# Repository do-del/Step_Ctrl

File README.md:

# Step_Ctrl
向XDrive和稚晖君的STEP-CTRL学习项目

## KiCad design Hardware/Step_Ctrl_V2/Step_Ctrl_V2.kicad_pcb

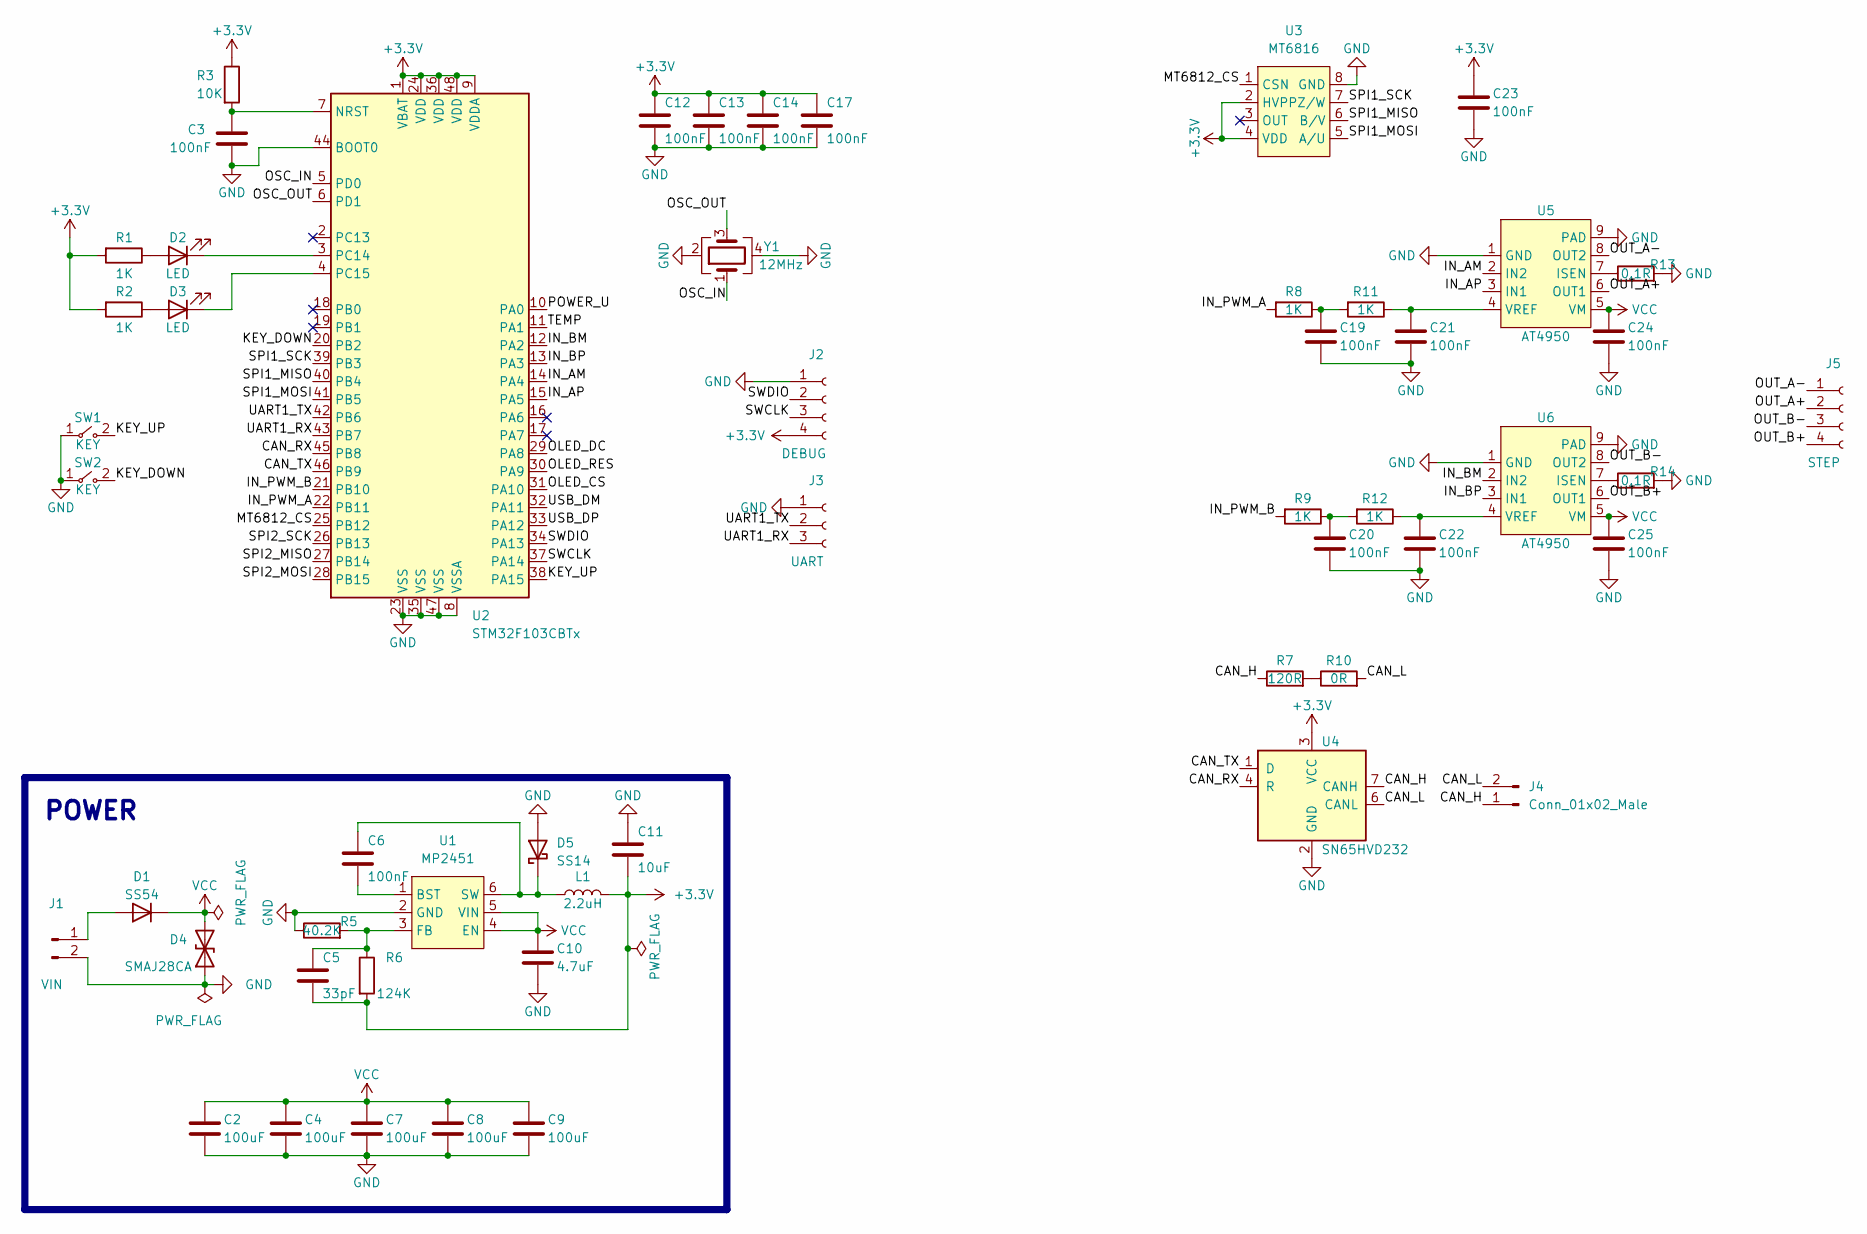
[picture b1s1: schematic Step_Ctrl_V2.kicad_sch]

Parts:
C2, C4, C7, C8, C9: 100uF; C_1210_3225Metric
C3, C6, C12, C13, C14, C17, C19, C20, C21, C22, C23, C24, C25: 100nF; C_0603_1608Metric_Pad1.08x0.95mm_HandSolder
C5: 33pF; C_0603_1608Metric_Pad1.08x0.95mm_HandSolder
C10: 4.7uF; C_0603_1608Metric_Pad1.08x0.95mm_HandSolder
C11: 10uF; C_0603_1608Metric_Pad1.08x0.95mm_HandSolder
D1: SS54; D_SMA
D2, D3: LED; LED_0603_1608Metric_Pad1.05x0.95mm_HandSolder
D4: SMAJ28CA; D_SMA
D5: SS14; D_SOD-323
J1: VIN; PH2.0mm-2P-WT
J2: DEBUG; JST_SH_SM04B-SRSS-TB_1x04-1MP_P1.00mm_Horizontal
J3: UART; JST_SH_SM03B-SRSS-TB_1x03-1MP_P1.00mm_Horizontal
J4: Conn_01x02_Male; SH1.0_01x02P_WT
J5: STEP; PH2.0mm-4P-WT
L1: 2.2uH; IND_CD32
R1, R2, R8, R9, R11, R12: 1K; R_0603_1608Metric_Pad0.98x0.95mm_HandSolder
R3: 10K; R_0603_1608Metric_Pad0.98x0.95mm_HandSolder
R5: 40.2K; R_0603_1608Metric_Pad0.98x0.95mm_HandSolder
R6: 124K; R_0603_1608Metric_Pad0.98x0.95mm_HandSolder
R7: 120R; R_0603_1608Metric_Pad0.98x0.95mm_HandSolder
R10: 0R; R_0402_1005Metric
R13, R14: 0.1R; R_1206_3216Metric
SW1, SW2: KEY; SW_3x4
U1: MP2451; SOT-23-6
U2: STM32F103CBTx; LQFP-48_7x7mm_P0.5mm
U3: MT6816; SOP-8
U4: SN65HVD232; SOIC-8_3.9x4.9mm_P1.27mm
U5, U6: AT4950; ESOP8L
Y1: 12MHz; Crystal_SMD_3225-4Pin_3.2x2.5mm

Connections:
+3V3: C5.2, C11.1, C12.1, C13.1, C14.1, C17.1, C23.1, J2.4, L1.2, R1.2, R2.2, R3.1, R6.2, U2.1 (VBAT), U2.9 (VDDA), U2.24 (VDD), U2.36 (VDD), U2.48 (VDD), U3.2 (HVPP), U3.4 (VDD), U4.3 (VCC)
/CAN_H: J4.1, R7.1, U4.7 (CANH)
/CAN_L: J4.2, R10.2, U4.6 (CANL)
/CAN_RX: U2.45 (PB8), U4.4 (R)
/CAN_TX: U2.46 (PB9), U4.1 (D)
/IN_AM: U2.14 (PA4), U5.2 (IN2)
/IN_AP: U2.15 (PA5), U5.3 (IN1)
/IN_BM: U2.12 (PA2), U6.2 (IN2)
/IN_BP: U2.13 (PA3), U6.3 (IN1)
/IN_PWM_A: R8.2, U2.22 (PB11)
/IN_PWM_B: R9.2, U2.21 (PB10)
/KEY_DOWN: SW2.2 (B), U2.20 (PB2)
/KEY_UP: SW1.2 (B), U2.38 (PA15)
/MT6812_CS: U2.25 (PB12), U3.1 (CSN)
/OLED_CS: U2.31 (PA10)
/OLED_DC: U2.29 (PA8)
/OLED_RES: U2.30 (PA9)
/OSC_IN: U2.5 (PD0), Y1.1
/OSC_OUT: U2.6 (PD1), Y1.3
/OUT_A+: J5.2, U5.6 (OUT1)
/OUT_A-: J5.1, U5.8 (OUT2)
/OUT_B+: J5.4, U6.6 (OUT1)
/OUT_B-: J5.3, U6.8 (OUT2)
/POWER_U: U2.10 (PA0)
/SPI1_MISO: U2.40 (PB4), U3.6 (B/V)
/SPI1_MOSI: U2.41 (PB5), U3.5 (A/U)
/SPI1_SCK: U2.39 (PB3), U3.7 (Z/W)
/SPI2_MISO: U2.27 (PB14)
/SPI2_MOSI: U2.28 (PB15)
/SPI2_SCK: U2.26 (PB13)
/SWCLK: J2.3, U2.37 (PA14)
/SWDIO: J2.2, U2.34 (PA13)
/TEMP: U2.11 (PA1)
/UART1_RX: J3.3, U2.43 (PB7)
/UART1_TX: J3.2, U2.42 (PB6)
/USB_DM: U2.32 (PA11)
/USB_DP: U2.33 (PA12)
GND: C2.2, C3.2, C4.2, C7.2, C8.2, C9.2, C10.2, C11.2, C12.2, C13.2, C14.2, C17.2, C19.2, C20.2, C21.2, C22.2, C23.2, C24.2, C25.2, D4.1 (A1), D5.2 (A), J1.2, J2.1, J3.1, R5.1, R13.2, R14.2, SW1.1 (A), SW2.1 (A), U1.2 (GND), U2.8 (VSSA), U2.23 (VSS), U2.35 (VSS), U2.44 (BOOT0), U2.47 (VSS), U3.8 (GND), U4.2 (GND), U5.1 (GND), U5.9 (PAD), U6.1 (GND), U6.9 (PAD), Y1.2, Y1.4
unnamed: C3.1, R3.2, U2.7 (NRST)
unnamed: C5.1, R5.2, R6.1, U1.3 (FB)
unnamed: C6.1, D5.1 (K), L1.1, U1.6 (SW)
unnamed: C6.2, U1.1 (BST)
unnamed: C19.1, R8.1, R11.2
unnamed: C20.1, R9.1, R12.2
unnamed: C21.1, R11.1, U5.4 (VREF)
unnamed: C22.1, R12.1, U6.4 (VREF)
unnamed: D1.2 (A), J1.1
unnamed: D2.1 (K), U2.3 (PC14)
unnamed: D2.2 (A), R1.1
unnamed: D3.1 (K), U2.4 (PC15)
unnamed: D3.2 (A), R2.1
unnamed: R7.2, R10.1
unnamed: R13.1, U5.7 (ISEN)
unnamed: R14.1, U6.7 (ISEN)
VCC: C2.1, C4.1, C7.1, C8.1, C9.1, C10.1, C24.1, C25.1, D1.1 (K), D4.2 (A2), U1.4 (EN), U1.5 (VIN), U5.5 (VM), U6.5 (VM)

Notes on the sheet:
POWER

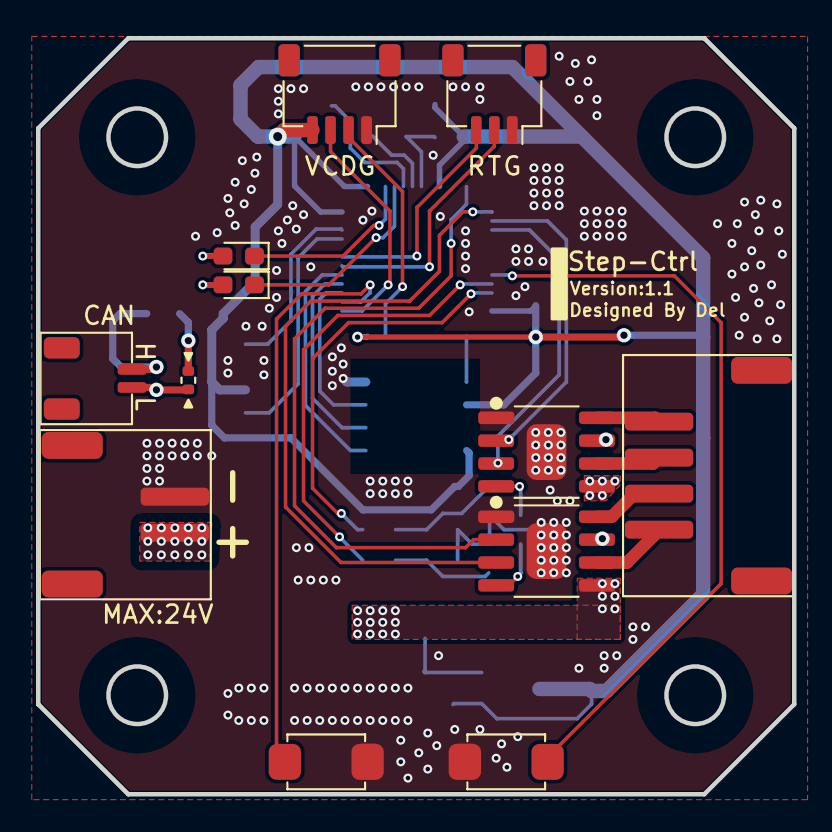
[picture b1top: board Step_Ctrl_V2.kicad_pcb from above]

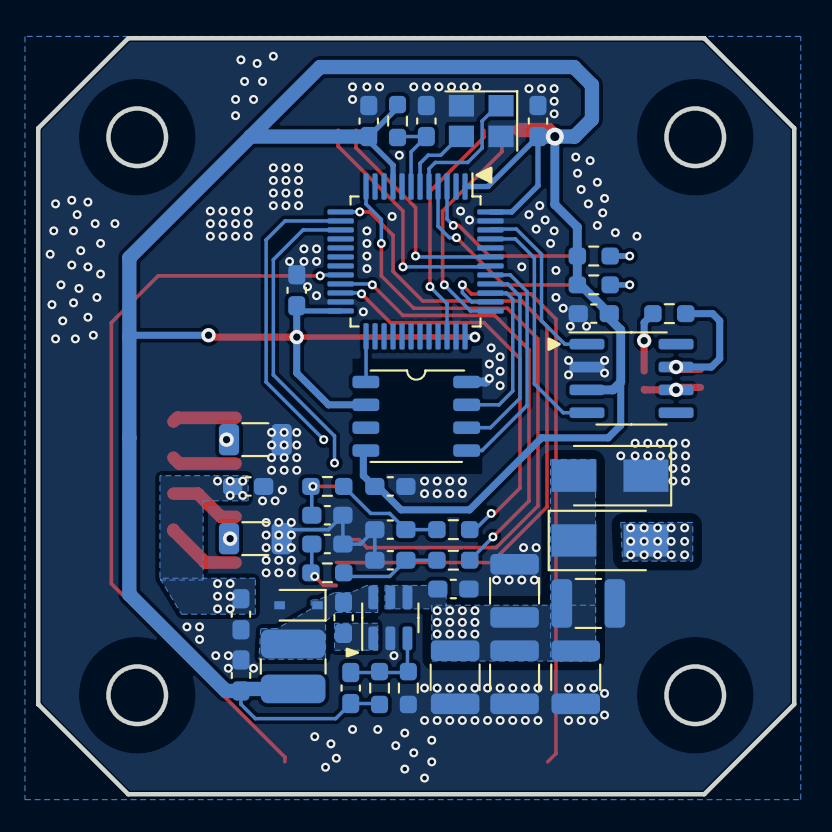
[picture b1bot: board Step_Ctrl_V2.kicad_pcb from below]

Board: 2 copper layers, 42.0 x 42.0 mm, 54 parts (42 on the bottom side), 45 nets.

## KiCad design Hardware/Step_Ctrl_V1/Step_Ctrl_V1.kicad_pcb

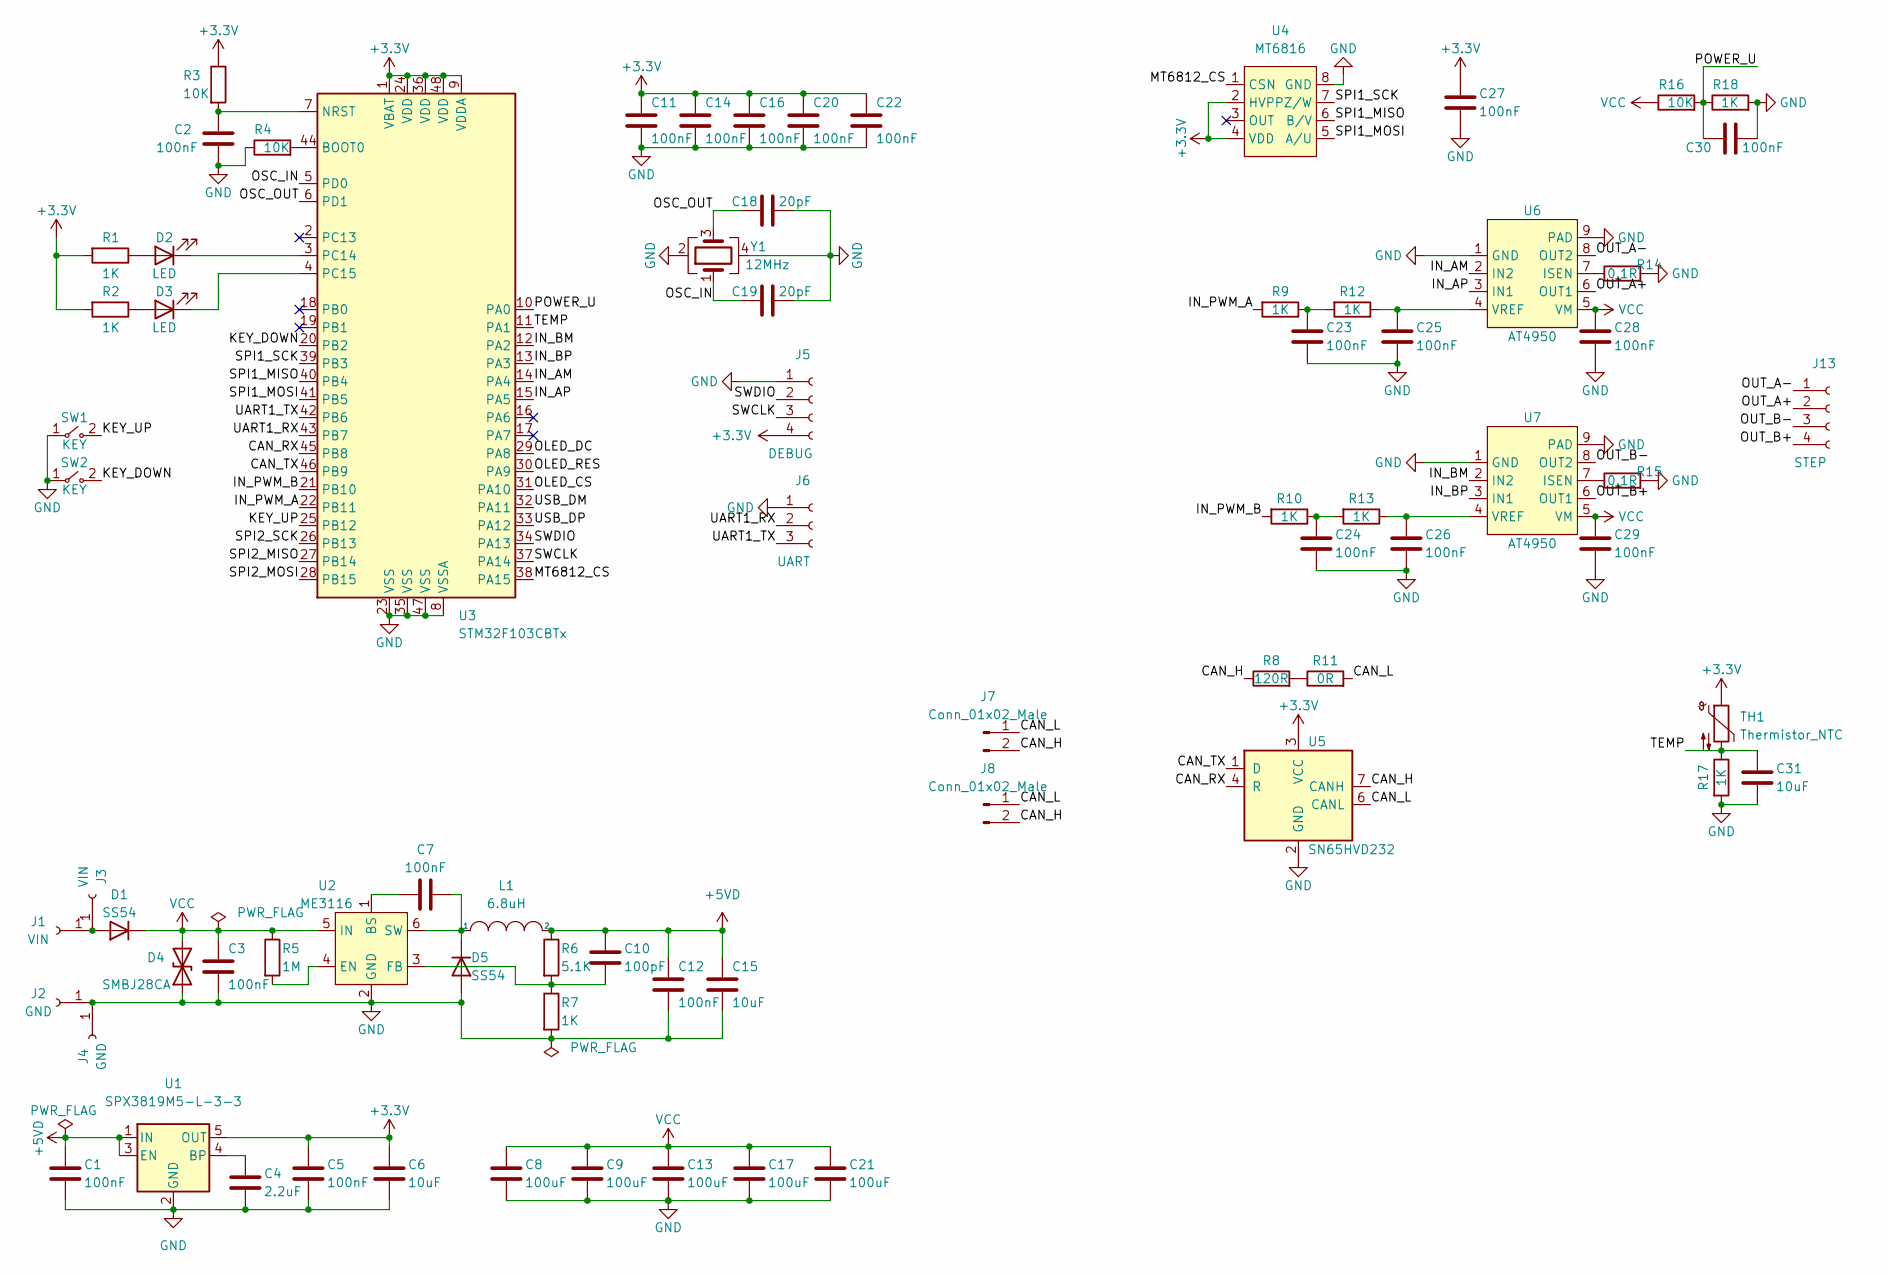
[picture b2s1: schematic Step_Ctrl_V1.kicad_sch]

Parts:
C1, C2, C3, C5, C7, C11, C12, C14, C16, C20, C22, C23, C24, C25, C26, C27, C28, C29, C30: 100nF; C_0603_1608Metric_Pad1.08x0.95mm_HandSolder
C4: 2.2uF; C_0603_1608Metric_Pad1.08x0.95mm_HandSolder
C6, C15, C31: 10uF; C_0603_1608Metric_Pad1.08x0.95mm_HandSolder
C8, C9, C13, C17, C21: 100uF; C_1210_3225Metric
C10: 100pF; C_0603_1608Metric_Pad1.08x0.95mm_HandSolder
C18, C19: 20pF; C_0603_1608Metric_Pad1.08x0.95mm_HandSolder
D1, D5: SS54; D_SMA
D2, D3: LED; LED_0603_1608Metric_Pad1.05x0.95mm_HandSolder
D4: SMBJ28CA; D_SMB
J1, J3: VIN; PAD_RECT
J2, J4: GND; PAD_RECT
J5: DEBUG; SH1.0mm_4P_WT
J6: UART; JST_SH_SM03B-SRSS-TB_1x03-1MP_P1.00mm_Horizontal
J7, J8: Conn_01x02_Male; SH1.0_01x02P_WT
J13: STEP; PH2.0mm-4P-WT
L1: 6.8uH; IND0420
R1, R2, R7, R9, R10, R12, R13, R17, R18: 1K; R_0603_1608Metric_Pad0.98x0.95mm_HandSolder
R3, R4, R16: 10K; R_0603_1608Metric_Pad0.98x0.95mm_HandSolder
R5: 1M; R_0603_1608Metric_Pad0.98x0.95mm_HandSolder
R6: 5.1K; R_0603_1608Metric_Pad0.98x0.95mm_HandSolder
R8: 120R; R_0603_1608Metric_Pad0.98x0.95mm_HandSolder
R11: 0R; R_0402_1005Metric
R14, R15: 0.1R; R_1206_3216Metric
SW1, SW2: KEY; SW_3x4
TH1: Thermistor_NTC; R_0603_1608Metric_Pad0.98x0.95mm_HandSolder
U1: SPX3819M5-L-3-3; SOT-23-5
U2: ME3116; SOT-23-6
U3: STM32F103CBTx; LQFP-48_7x7mm_P0.5mm
U4: MT6816; SOP-8
U5: SN65HVD232; SOIC-8_3.9x4.9mm_P1.27mm
U6, U7: AT4950; ESOP8L
Y1: 12MHz; Crystal_SMD_3225-4Pin_3.2x2.5mm

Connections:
+3V3: C5.1, C6.1, C11.1, C14.1, C16.1, C20.1, C22.1, C27.1, J5.4, R1.2, R2.2, R3.1, TH1.1, U1.5 (OUT), U3.1 (VBAT), U3.9 (VDDA), U3.24 (VDD), U3.36 (VDD), U3.48 (VDD), U4.2 (HVPP), U4.4 (VDD), U5.3 (VCC)
+5VD: C1.1, C10.2, C12.1, C15.1, L1.2, R6.1, U1.1 (IN), U1.3 (EN)
/CAN_H: J7.2, J8.2, R8.1, U5.7 (CANH)
/CAN_L: J7.1, J8.1, R11.2, U5.6 (CANL)
/CAN_RX: U3.45 (PB8), U5.4 (R)
/CAN_TX: U3.46 (PB9), U5.1 (D)
/IN_AM: U3.14 (PA4), U6.2 (IN2)
/IN_AP: U3.15 (PA5), U6.3 (IN1)
/IN_BM: U3.12 (PA2), U7.2 (IN2)
/IN_BP: U3.13 (PA3), U7.3 (IN1)
/IN_PWM_A: R9.2, U3.22 (PB11)
/IN_PWM_B: R10.2, U3.21 (PB10)
/KEY_DOWN: SW2.2 (B), U3.20 (PB2)
/KEY_UP: SW1.2 (B), U3.25 (PB12)
/MT6812_CS: U3.38 (PA15), U4.1 (CSN)
/OLED_CS: U3.31 (PA10)
/OLED_DC: U3.29 (PA8)
/OLED_RES: U3.30 (PA9)
/OSC_IN: C19.1, U3.5 (PD0), Y1.1
/OSC_OUT: C18.1, U3.6 (PD1), Y1.3
/OUT_A+: J13.2, U6.6 (OUT1)
/OUT_A-: J13.1, U6.8 (OUT2)
/OUT_B+: J13.4, U7.6 (OUT1)
/OUT_B-: J13.3, U7.8 (OUT2)
/POWER_U: C30.1, R16.2, R18.1, U3.10 (PA0)
/SPI1_MISO: U3.40 (PB4), U4.6 (B/V)
/SPI1_MOSI: U3.41 (PB5), U4.5 (A/U)
/SPI1_SCK: U3.39 (PB3), U4.7 (Z/W)
/SPI2_MISO: U3.27 (PB14)
/SPI2_MOSI: U3.28 (PB15)
/SPI2_SCK: U3.26 (PB13)
/SWCLK: J5.3, U3.37 (PA14)
/SWDIO: J5.2, U3.34 (PA13)
/TEMP: C31.1, R17.1, TH1.2, U3.11 (PA1)
/UART1_RX: J6.2, U3.43 (PB7)
/UART1_TX: J6.3, U3.42 (PB6)
/USB_DM: U3.32 (PA11)
/USB_DP: U3.33 (PA12)
GND: C1.2, C2.2, C3.2, C4.2, C5.2, C6.2, C8.2, C9.2, C11.2, C12.2, C13.2, C14.2, C15.2, C16.2, C17.2, C18.2, C19.2, C20.2, C21.2, C22.2, C23.2, C24.2, C25.2, C26.2, C27.2, C28.2, C29.2, C30.2, C31.2, D4.1 (A1), D5.2 (A), J2.1, J4.1, J5.0, J5.1, J6.1, J6.MP, J7.4, J8.3, J13.0, R4.1, R7.2, R14.2, R15.2, R17.2, R18.2, SW1.1 (A), SW2.1 (A), U1.2 (GND), U2.2 (GND), U3.8 (VSSA), U3.23 (VSS), U3.35 (VSS), U3.47 (VSS), U4.8 (GND), U5.2 (GND), U6.1 (GND), U6.9 (PAD), U7.1 (GND), U7.9 (PAD), Y1.2, Y1.4
unnamed: C2.1, R3.2, U3.7 (NRST)
unnamed: C4.1, U1.4 (BP)
unnamed: C7.1, U2.1 (BS)
unnamed: C7.2, D5.1 (K), L1.1, U2.6 (SW)
unnamed: C10.1, R6.2, R7.1, U2.3 (FB)
unnamed: C23.1, R9.1, R12.2
unnamed: C24.1, R10.1, R13.2
unnamed: C25.1, R12.1, U6.4 (VREF)
unnamed: C26.1, R13.1, U7.4 (VREF)
unnamed: D1.2 (A), J1.1, J3.1, J7.3, J8.4, J13.0
unnamed: D2.1 (K), U3.3 (PC14)
unnamed: D2.2 (A), R1.1
unnamed: D3.1 (K), U3.4 (PC15)
unnamed: D3.2 (A), R2.1
unnamed: R4.2, U3.44 (BOOT0)
unnamed: R5.2, U2.4 (EN)
unnamed: R8.2, R11.1
unnamed: R14.1, U6.7 (ISEN)
unnamed: R15.1, U7.7 (ISEN)
VCC: C3.1, C8.1, C9.1, C13.1, C17.1, C21.1, C28.1, C29.1, D1.1 (K), D4.2 (A2), R5.1, R16.1, U2.5 (IN), U6.5 (VM), U7.5 (VM)

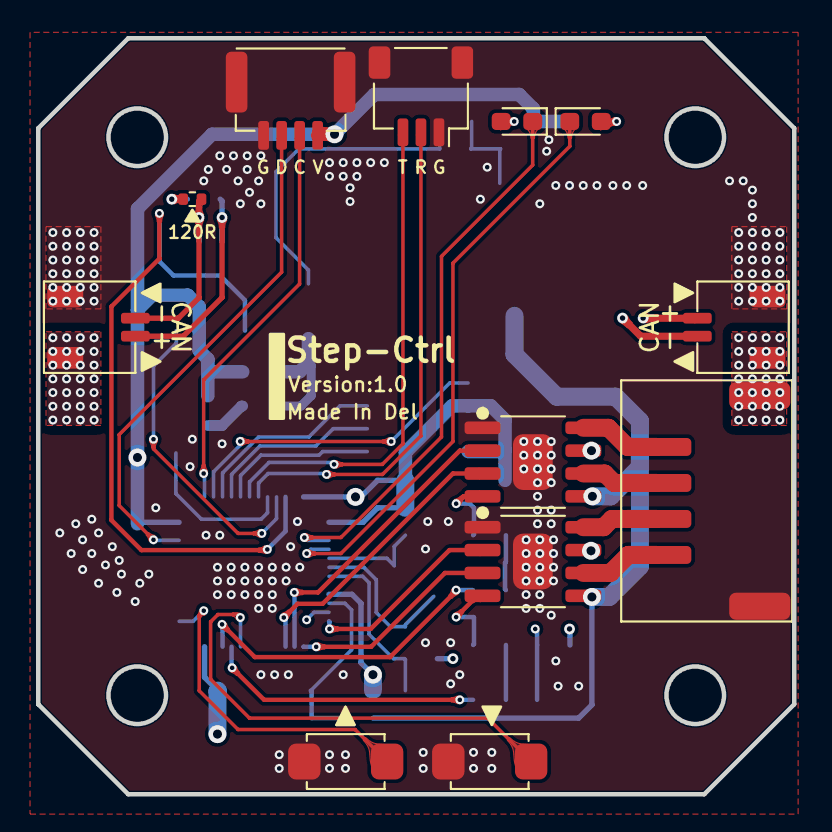
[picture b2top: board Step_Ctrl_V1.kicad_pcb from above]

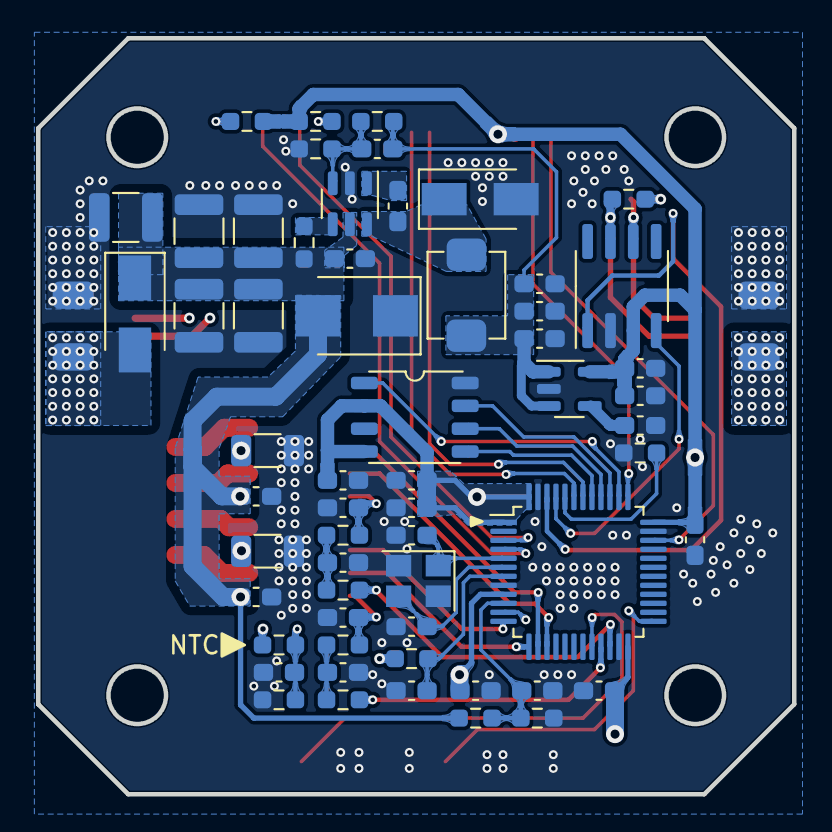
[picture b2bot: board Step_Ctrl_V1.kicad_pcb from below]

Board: 4 copper layers, 42.0 x 42.0 mm, 75 parts (63 on the bottom side), 51 nets.

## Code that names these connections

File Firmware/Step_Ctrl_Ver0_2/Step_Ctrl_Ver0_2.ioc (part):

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Mcu.Name=STM32F103C(8-B)Tx
Mcu.Package=LQFP48
Mcu.UserName=STM32F103CBTx
PA13.Mode=Serial_Wire
PA13.Signal=SYS_JTMS-SWDIO
PA14.Mode=Serial_Wire
PA14.Signal=SYS_JTCK-SWCLK
PA15.GPIOParameters=GPIO_PuPd
PA15.GPIO_PuPd=GPIO_PULLUP
PA15.Signal=GPIO_Input
PA2.GPIOParameters=GPIO_Speed
PA2.GPIO_Speed=GPIO_SPEED_FREQ_HIGH
PA2.Signal=GPIO_Output
PA3.GPIOParameters=GPIO_Speed
PA3.GPIO_Speed=GPIO_SPEED_FREQ_HIGH
PA3.Signal=GPIO_Output
PA4.GPIOParameters=GPIO_Speed
PA4.GPIO_Speed=GPIO_SPEED_FREQ_HIGH
PA4.Signal=GPIO_Output
PA5.GPIOParameters=GPIO_Speed
PA5.GPIO_Speed=GPIO_SPEED_FREQ_HIGH
PA5.Signal=GPIO_Output
PB10.Signal=S_TIM2_CH3
PB11.Signal=S_TIM2_CH4
PB12.GPIOParameters=GPIO_Speed,PinState
PB12.GPIO_Speed=GPIO_SPEED_FREQ_HIGH
PB12.PinState=GPIO_PIN_SET
PB12.Signal=GPIO_Output
PB2.GPIOParameters=GPIO_PuPd
PB2.GPIO_PuPd=GPIO_PULLUP
PB2.Signal=GPIO_Input
PB3.Mode=Full_Duplex_Master
PB3.Signal=SPI1_SCK
PB4.Mode=Full_Duplex_Master
PB4.Signal=SPI1_MISO
PB5.Mode=Full_Duplex_Master
PB5.Signal=SPI1_MOSI
PB6.Mode=Asynchronous
PB6.Signal=USART1_TX
PB7.Mode=Asynchronous
PB7.Signal=USART1_RX
PB8.Mode=CAN_Activate
PB8.Signal=CAN_RX
PB9.Mode=CAN_Activate
PB9.Signal=CAN_TX
PC14-OSC32_IN.GPIOParameters=PinState
PC14-OSC32_IN.PinState=GPIO_PIN_SET
PC14-OSC32_IN.Signal=GPIO_Output
PC15-OSC32_OUT.GPIOParameters=PinState
PC15-OSC32_OUT.PinState=GPIO_PIN_SET
PC15-OSC32_OUT.Signal=GPIO_Output
PD0-OSC_IN.Mode=HSE-External-Oscillator
PD0-OSC_IN.Signal=RCC_OSC_IN
PD1-OSC_OUT.Mode=HSE-External-Oscillator
PD1-OSC_OUT.Signal=RCC_OSC_OUT
RCC.HSE_VALUE=12000000
RCC.SYSCLKFreq_VALUE=72000000
RCC.SYSCLKSource=RCC_SYSCLKSOURCE_PLLCLK
board=custom

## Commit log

2023-01-06 添加第一版PCB设计文件，PCB尚未打样
2023-01-12 测试DXF
2023-02-01 添加LED测试工程
2023-02-01 测试程序添加Uart1发送测试
2023-02-02 V1.0硬件存在严重的磁场干扰，现已做一定精简并重新设计PCB，等待打样验证
2023-02-07 1.1版PCB完成焊接，通过MT6816测试
2023-02-08 添加PCB上壳模型文件
2023-02-14 添加v0.2版固件源码，大部分搬运XDrive
2023-02-14 测试只有定位时的震动
2023-02-14 尝试修改PID，还未达到稳定状态
2023-02-15 找到震动原因，原H桥驱动芯片AT8236Vref引脚不起作用，更换其它型号后测试通过
2023-02-16 完成CAN总线收发功能程序测试
2023-02-28 添加20电机PCB原理图
